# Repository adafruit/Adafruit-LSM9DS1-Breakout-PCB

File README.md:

## Adafruit LSM9DS1 Breakout PCB

<a href="http://www.adafruit.com/products/3387"><br/>
Click here to purchase one from the Adafruit shop</a>

PCB files for the Adafruit LSM9DS1 Breakout. Format is EagleCAD schematic and board layout
* https://www.adafruit.com/product/3387

### Description

Add motion, direction and orientation sensing to your Arduino project with this all-in-one 9-DOF sensor. Inside the chip are three sensors, one is a classic 3-axis accelerometer, which can tell you which direction is down towards the Earth (by measuring gravity) or how fast the board is accelerating in 3D space. The other is a 3-axis magnetometer that can sense where the strongest magnetic force is coming from, generally used to detect magnetic north. The third is a 3-axis gyroscope that can measure spin and twist. By combining this data you can REALLY orient yourself.

We've carried the LSM9DS0 from ST for a while, and the LSM9DS1 is their latest offering. We thought this could really make for a great breakout, at a very nice price! Design your own activity or motion tracker with all the data... We spun up a breakout board that has all the extra circuitry you'll want, for use with an Arduino (or other microcontroller).

### License

Adafruit invests time and resources providing this open source design, please support Adafruit and open-source hardware by purchasing products from [Adafruit](https://www.adafruit.com)!

Designed by Limor Fried/Ladyada for Adafruit Industries.

Creative Commons Attribution/Share-Alike, all text above must be included in any redistribution. See license.txt for additional details.

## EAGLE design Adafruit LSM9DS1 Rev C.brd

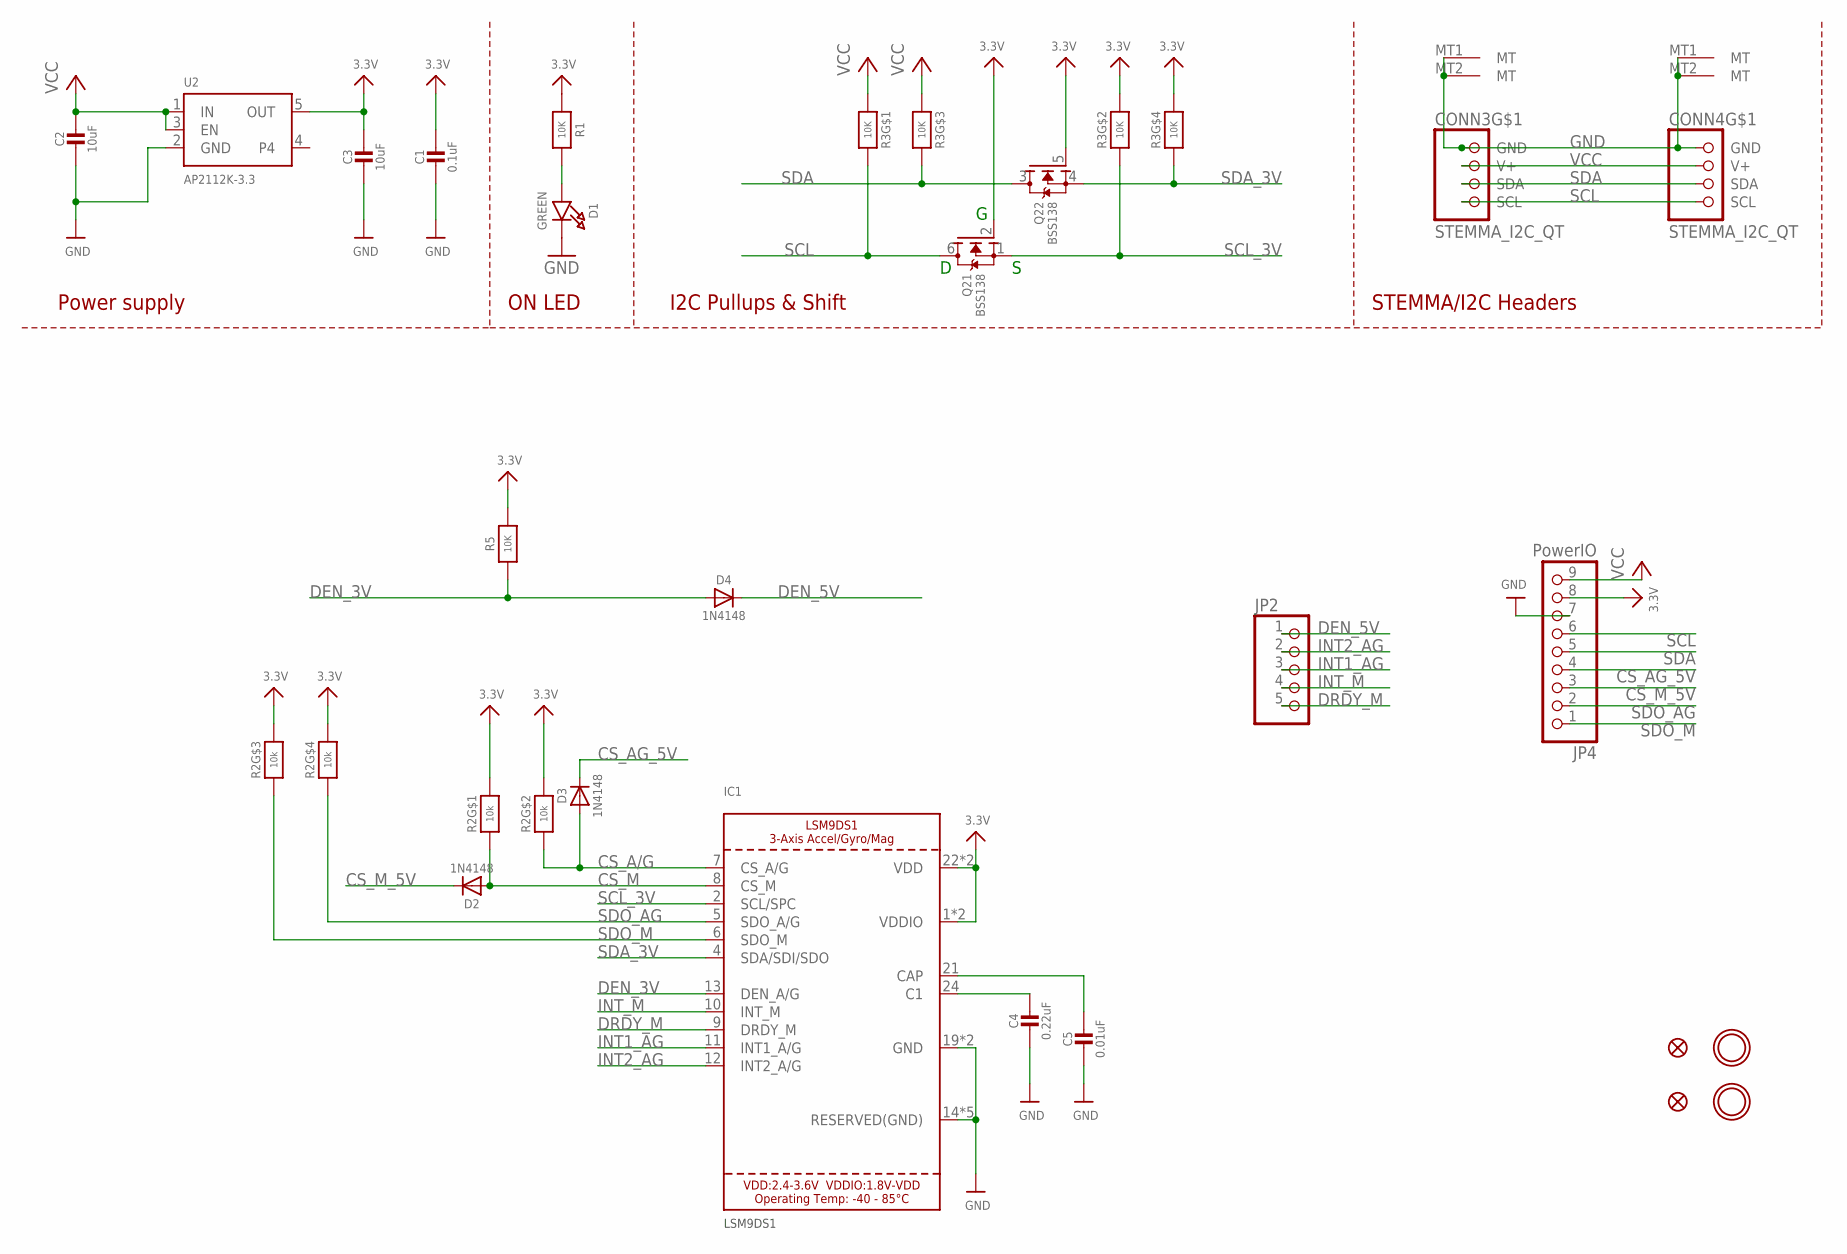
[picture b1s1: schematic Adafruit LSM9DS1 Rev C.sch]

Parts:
C1: 0.1uF; 0603-NO
C2: 10uF; _0805MP
C3: 10uF; 0805-NO
C4: 0.22uF; 0603-NO
C5: 0.01uF; 0603-NO
CONN3, CONN4: STEMMA_I2C_QT; JST_SH4
D1: GREEN; CHIPLED_0603_NOOUTLINE
D2, D3, D4: 1N4148; SOD-323
FID3, FID4: FIDUCIAL_1MM
IC1: LSM9DS1; LGA24_3.5X3.1MM
JP2: HEADER-1X570MIL; 1X05_ROUND_70
JP4: PowerIO; 1X09_ROUND_70
Q2: BSS138; SOT363
R1, R5: 10K; 0603-NO
R2: 10k; RESPACK_4X0603
R3: 10K; RESPACK_4X0603
U2: AP2112K-3.3; SOT23-5
U$1, U$17: MOUNTINGHOLE2.5; MOUNTINGHOLE_2.5_PLATED

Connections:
3.3V: C1.1, C3.1, IC1.1 (VDDIO), IC1.3 (VDDIO), IC1.22 (VDD), IC1.23 (VDD), JP4.8, Q2.2 (G), Q2.5 (G), R1.1, R2.5 (2), R2.6 (2), R2.7 (2), R2.8 (2), R3.2 (1), R3.4 (1), R5.2, U2.5 (OUT)
C1: C4.1, IC1.24 (C1)
CAP: C5.1, IC1.21 (CAP)
CS_A/G: D3.A, IC1.7 (CS_A/G), R2.2 (1)
CS_AG_5V: D3.C, JP4.4
CS_M: D2.A, IC1.8 (CS_M), R2.1
CS_M_5V: D2.C, JP4.3
DEN_3V: D4.A, IC1.13 (DEN_A/G), R5.1
DEN_5V: D4.C, JP2.1
DRDY_M: IC1.9 (DRDY_M), JP2.5
GND: C1.2, C2.2, C3.2, C4.2, C5.2, CONN3.1 (GND), CONN3.MT1 (MT), CONN3.MT2 (MT), CONN4.1 (GND), CONN4.MT1 (MT), CONN4.MT2 (MT), D1.C, IC1.14 (RESERVED(GND)), IC1.15 (RESERVED(GND)), IC1.16 (RESERVED(GND)), IC1.17 (RESERVED(GND)), IC1.18 (RESERVED(GND)), IC1.19 (GND), IC1.20 (GND), JP4.7, U2.2 (GND)
INT1_AG: IC1.11 (INT1_A/G), JP2.3
INT2_AG: IC1.12 (INT2_A/G), JP2.2
INT_M: IC1.10 (INT_M), JP2.4
unnamed: D1.A, R1.2
SCL: CONN3.4 (SCL), CONN4.4 (SCL), JP4.6, Q2.6 (D), R3.8 (2)
SCL_3V: IC1.2 (SCL/SPC), Q2.1 (S), R3.7 (2)
SDA: CONN3.3 (SDA), CONN4.3 (SDA), JP4.5, Q2.3 (D), R3.6 (2)
SDA_3V: IC1.4 (SDA/SDI/SDO), Q2.4 (S), R3.5 (2)
SDO_AG: IC1.5 (SDO_A/G), JP4.2, R2.4 (1)
SDO_M: IC1.6 (SDO_M), JP4.1, R2.3 (1)
VCC: C2.1, CONN3.2 (V+), CONN4.2 (V+), JP4.9, R3.1, R3.3 (1), U2.1 (IN), U2.3 (EN)

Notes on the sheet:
I2C Pullups & Shift
STEMMA/I2C Headers
ON LED
Power supply

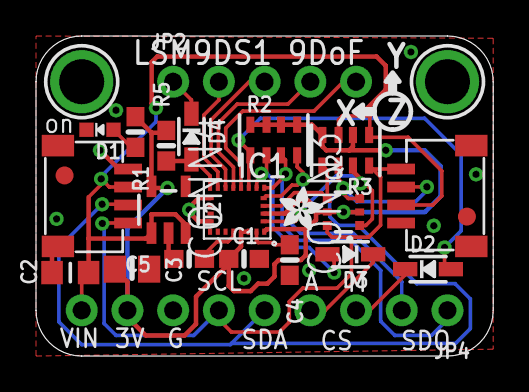
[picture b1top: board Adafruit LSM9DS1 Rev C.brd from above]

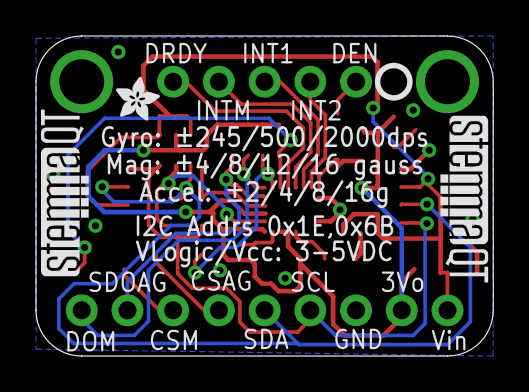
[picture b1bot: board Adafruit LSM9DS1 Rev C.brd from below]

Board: 2 copper layers, 25.4 x 17.8 mm, 29 parts (4 on the bottom side), 22 nets.

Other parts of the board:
U$10, U$16: ADAFRUIT_2.5MM
U$25: PCBFEAT-REV-040
U$30, U$31: STEMMAQT

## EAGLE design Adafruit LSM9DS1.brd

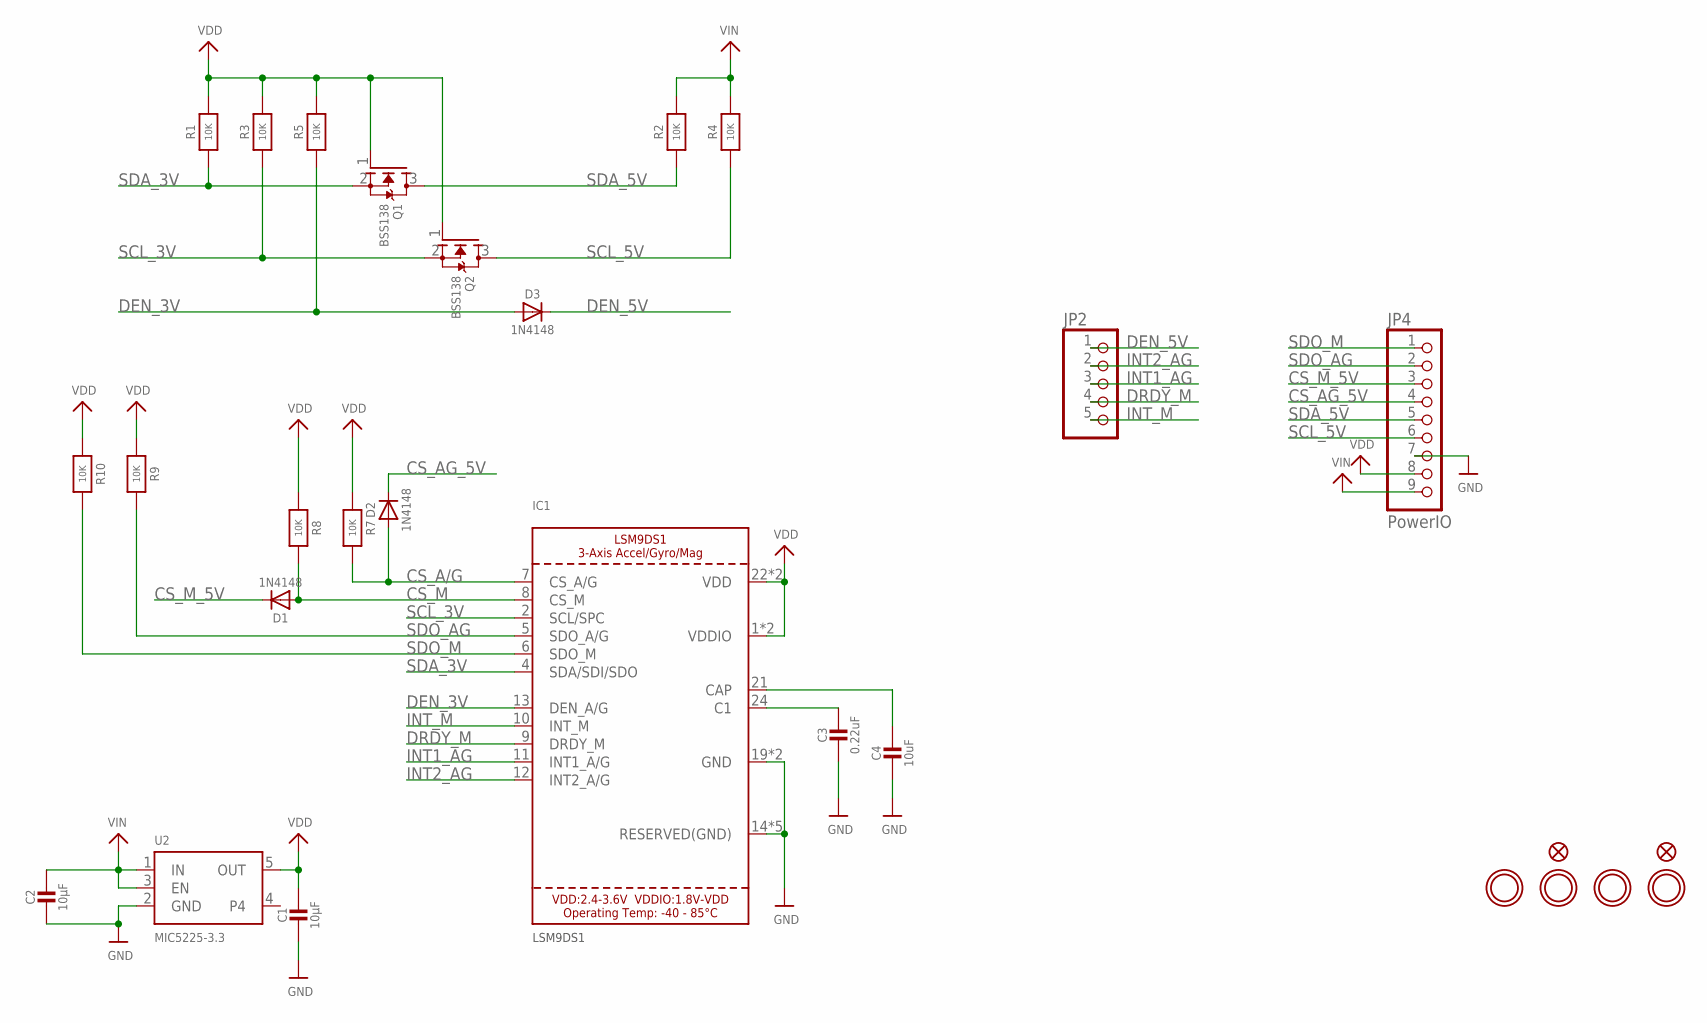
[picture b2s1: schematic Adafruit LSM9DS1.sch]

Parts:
C1, C2: 10µF; 0805-NO
C3: 0.22uF; 0805_10MGAP
C4: 10uF; 0805-NO
D1, D2, D3: 1N4148; SOD-323
FID1, FID3: FIDUCIAL""; FIDUCIAL_1MM
IC1: LSM9DS1; LGA24_3.5X3.1MM
JP2: HEADER-1X570MIL; 1X05_ROUND_70
JP4: PowerIO; 1X09_ROUND_70
Q1, Q2: BSS138; SOT23-WIDE
R1, R9: 10K; 0805_10MGAP
R2, R3, R4, R5, R7, R8, R10: 10K; 0805-NO
U2: MIC5225-3.3; SOT23-5
U$4, U$5, U$6, U$7: MOUNTINGHOLE2.5; MOUNTINGHOLE_2.5_PLATED

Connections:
C1: C3.1, IC1.24 (C1)
CAP: C4.1, IC1.21 (CAP)
CS_A/G: D2.A, IC1.7 (CS_A/G), R7.2
CS_AG_5V: D2.C, JP4.4
CS_M: D1.A, IC1.8 (CS_M), R8.2
CS_M_5V: D1.C, JP4.3
DEN_3V: D3.A, IC1.13 (DEN_A/G), R5.1
DEN_5V: D3.C, JP2.1
DRDY_M: IC1.9 (DRDY_M), JP2.4
GND: C1.2, C2.2, C3.2, C4.2, IC1.14 (RESERVED(GND)), IC1.15 (RESERVED(GND)), IC1.16 (RESERVED(GND)), IC1.17 (RESERVED(GND)), IC1.18 (RESERVED(GND)), IC1.19 (GND), IC1.20 (GND), JP4.7, U2.2 (GND)
INT1_AG: IC1.11 (INT1_A/G), JP2.3
INT2_AG: IC1.12 (INT2_A/G), JP2.2
INT_M: IC1.10 (INT_M), JP2.5
SCL_3V: IC1.2 (SCL/SPC), Q2.2 (S), R3.1
SCL_5V: JP4.6, Q2.3 (D), R4.1
SDA_3V: IC1.4 (SDA/SDI/SDO), Q1.2 (S), R1.1
SDA_5V: JP4.5, Q1.3 (D), R2.1
SDO_AG: IC1.5 (SDO_A/G), JP4.2, R9.2
SDO_M: IC1.6 (SDO_M), JP4.1, R10.2
VDD: C1.1, IC1.1 (VDDIO), IC1.3 (VDDIO), IC1.22 (VDD), IC1.23 (VDD), JP4.8, Q1.1 (G), Q2.1 (G), R1.2, R3.2, R5.2, R7.1, R8.1, R9.1, R10.1, U2.5 (OUT)
VIN: C2.1, JP4.9, R2.2, R4.2, U2.1 (IN), U2.3 (EN)

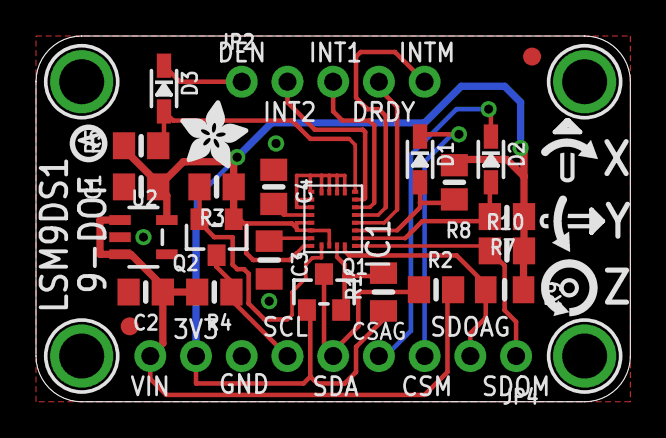
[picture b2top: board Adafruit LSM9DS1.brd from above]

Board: 2 copper layers, 33.0 x 20.3 mm, 31 parts (0 on the bottom side), 21 nets.

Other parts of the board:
U$14: SYMBOL_GYROXYZ_YREV_10MM
U$20: PCBFEAT-REV-040
U$23: ADAFRUIT_3.5MM

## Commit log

2017-02-01 init
2020-06-18 adding Rev C/Stemma QT version

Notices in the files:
parts and their libraries:
microbuilder: This work is placed in the public domain, and may be freely used for commercial and non-commercial work with the following conditions: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
